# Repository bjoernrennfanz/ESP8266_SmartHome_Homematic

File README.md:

# ESP8266_SmartHome_Switch
An SmartHome electronic switch with the ESP8266.

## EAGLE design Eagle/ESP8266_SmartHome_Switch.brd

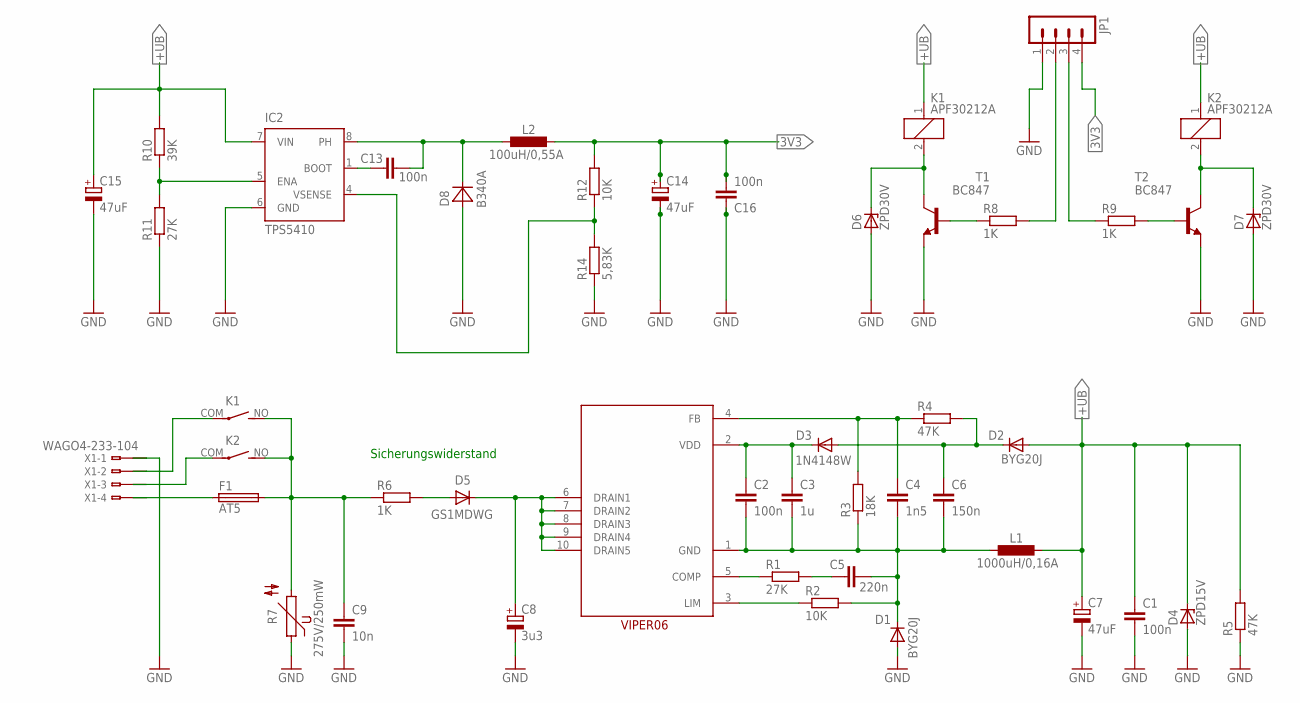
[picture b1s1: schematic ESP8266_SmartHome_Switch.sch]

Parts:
C1, C2, C13, C16: 100n; C0603; VOLTAGE 50V
C3: 1u; C0603; VOLTAGE 50V
C4: 1n5; C0603; VOLTAGE 25V
C5: 220n; C0603; VOLTAGE 50V
C6: 150n; C0603; VOLTAGE 50V
C7, C14, C15: 47uF; D/7343-31W; VOLTAGE 35V; PARTNUMBER T495X476K035ATE200
C8: 3u3; E5-10,5; PARTNUMBER 860021375007
C9: 10n; C7.5B4; PARTNUMBER MKP-X2 10N
D1, D2: BYG20J; DO-214AC
D3: 1N4148W; SOD-123_MINI-SMA
D4: ZPD15V; SMB
D5: GS1MDWG; DO214AC
D6, D7: ZPD30V; SMB
D8: B340A; SMA
F1: AT5; TR5
IC1: VIPER06HS; SSO10
IC2: TPS5410; D_R-PDSO-G08
JP1: MA04-1
K1, K2: APF30212A
L1: 1000uH/0,16A; POWER-CHOKE_WE-TPC; PARTNUMBER 744062102
L2: 100uH/0,55A; POWER-CHOKE_WE-TPC; PARTNUMBER 744062101
R1, R11: 27K; R0603
R2, R12: 10K; R0603
R3: 18K; R0603
R4, R5: 47K; R0603
R6: 1K; 0414V
R7: 275V/250mW; S07K275
R8, R9: 1K; R0603
R10: 39K; R0603
R14: 5,83K; R0603
T1, T2: BC847; SOT23
X1: WAGO4-233-104; 233-104

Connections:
3V3: C14.+, C16.2, JP1.4, L2.1, R12.2
+UB: C1.1, C7.+, C15.+, D2.A, D4.C, IC2.7 (VIN), K1.1, K2.1, L1.1, R5.2, R10.2
GND: C1.2, C7.-, C8.-, C9.2, C14.-, C15.-, C16.1, D1.A, D4.A, D6.A, D7.A, D8.A, IC2.6 (GND), JP1.1, R5.1, R7.1, R11.1, R14.1, T1.2 (E), T2.2 (E), X1.A1, X1.B1
unnamed: IC1.3 (LIM), R2.1
unnamed: IC1.5 (COMP), R1.1
unnamed: C5.1, R1.2
unnamed: C2.2, C3.2, C4.2, C5.2, C6.2, D1.C, IC1.1 (GND), L1.2, R2.2, R3.1
unnamed: C2.1, C3.1, D3.C, IC1.2 (VDD)
unnamed: C4.1, IC1.4 (FB), R3.2, R4.1
unnamed: C6.1, D2.C, D3.A, R4.2
unnamed: C8.+, D5.C, IC1.6 (DRAIN1), IC1.7 (DRAIN2), IC1.8 (DRAIN3), IC1.9 (DRAIN4), IC1.10 (DRAIN5)
unnamed: D5.A, R6.2
unnamed: C9.1, F1.2, K1.NO (S), K2.NO (S), R6.1, R7.2
unnamed: D6.C, K1.2, T1.3 (C)
unnamed: K1.COM, X1.A2 (A1), X1.B2 (B1)
unnamed: K2.COM, X1.A3 (A1), X1.B3 (B1)
unnamed: F1.1, X1.A4 (A1), X1.B4 (B1)
unnamed: JP1.2, R8.2
unnamed: D7.C, K2.2, T2.3 (C)
unnamed: R9.2, T2.1 (B)
unnamed: JP1.3, R9.1
unnamed: R8.1, T1.1 (B)
unnamed: IC2.5 (ENA), R10.1, R11.2
unnamed: C13.1, IC2.1 (BOOT)
unnamed: C13.2, D8.C, IC2.8 (PH), L2.2
unnamed: IC2.4 (VSENSE), R12.1, R14.2

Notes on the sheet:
Sicherungswiderstand

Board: 2 copper layers, 45 parts (0 on the bottom side), 26 nets, no tracks yet.

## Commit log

2016-11-10 Innitial import of eagle project for pcb & schematics
2016-11-11 Add VIPER06HS as part to SmartHome Eagle Library. Add some Eagle files to ignore list.
2017-01-03 Finish power part of ESP8266 SmartHome switch
2017-01-19 Add of subprojects and Eclipse projects
2017-01-23 First try with ContikiCore processes using ESP8266
2017-01-30 First compiling version with ContikiCore and autostart processes
2017-03-04 Removed ContikiCore for ESP8266 as submobule.
2017-03-05 First running program that collects DHT sensor data.
2017-04-17 Removed AskSin library and changed project name. Add README for project.
2017-04-17 Implemented telnet server deamon. Adding loopback of input characters for testing.
2017-04-20 Add of ringbuffer implementation.
2017-04-21 First version that reads complete lines from telnet socket.
2017-04-21 Improved line read function with lower memory consume.
2017-04-21 Moved ringbuffer into new drivers subfolder
2017-04-25 Work in progress on command-line parser.
2017-04-26 Reallocation of memory for command-line parsers now works.
2017-04-29 Add Eclipse and Visual Studio temporary files to .gitignore
2017-04-30 Implemented driver for CC1101 modules
2017-05-01 Add license headers to all files.
2017-05-01 Add drivers subproject and ringbuffer implementation.
2017-05-01 Add malloc implementation that uses static buffer. Add Visual Studio project and solution files.
2017-05-01 Malloc static buffer implementation works now.
2017-05-02 Add componet for TADO v2 api and Homematic protocol implementations. Begin work on Homematic protocol
2017-05-09 Add partial implementation of homematic protocol
